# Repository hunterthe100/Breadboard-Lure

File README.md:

# Breadboard-Lure (Not named yet or finished)
A lure for the MinnowBoard Max & MinnowBoard Turbot.  Copyright (C) 2015 Smallworks, LLC

This design is made with [EAGLE CAD](http://www.cadsoftusa.com/eagle-pcb-design-software/about-eagle/) 

This work is licensed under a Creative Commons Attribution-ShareAlike 4.0 International License
[  
*Licensing CC BY-SA 4.0*](http://creativecommons.org/licenses/by-sa/4.0/)

It may be used for Educational, Personal, or Commercial Use, provided you keep these notices,
attribution, and share-alike. When you apply these licenses to material you create, 
it meets the Freedom Defined definition of a "Free Cultural Work". 
Free cultural works are the ones that can be most readily used, shared, 
and remixed by others, and go furthest toward creating a commons of freely reusable materials.

-------------------------------------------------------------------------------------------

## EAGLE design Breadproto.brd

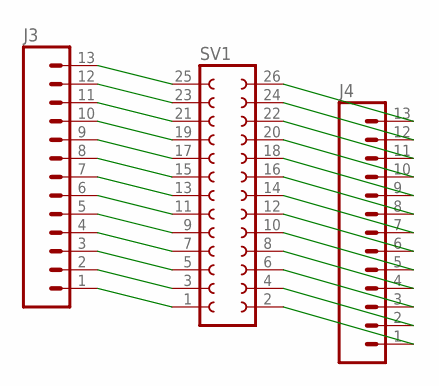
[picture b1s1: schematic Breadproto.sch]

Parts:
J3, J4: M13; 1X13
SV1: FE13-2

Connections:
unnamed: J3.1, SV1.1
unnamed: J3.2, SV1.3
unnamed: J3.3, SV1.5
unnamed: J3.4, SV1.7
unnamed: J3.5, SV1.9
unnamed: J3.6, SV1.11
unnamed: J3.7, SV1.13
unnamed: J3.8, SV1.15
unnamed: J3.9, SV1.17
unnamed: J3.10, SV1.19
unnamed: J3.11, SV1.21
unnamed: J3.12, SV1.23
unnamed: J3.13, SV1.25
unnamed: J4.1, SV1.2
unnamed: J4.2, SV1.4
unnamed: J4.3, SV1.6
unnamed: J4.4, SV1.8
unnamed: J4.5, SV1.10
unnamed: J4.6, SV1.12
unnamed: J4.7, SV1.14
unnamed: J4.8, SV1.16
unnamed: J4.9, SV1.18
unnamed: J4.10, SV1.20
unnamed: J4.11, SV1.22
unnamed: J4.12, SV1.24
unnamed: J4.13, SV1.26

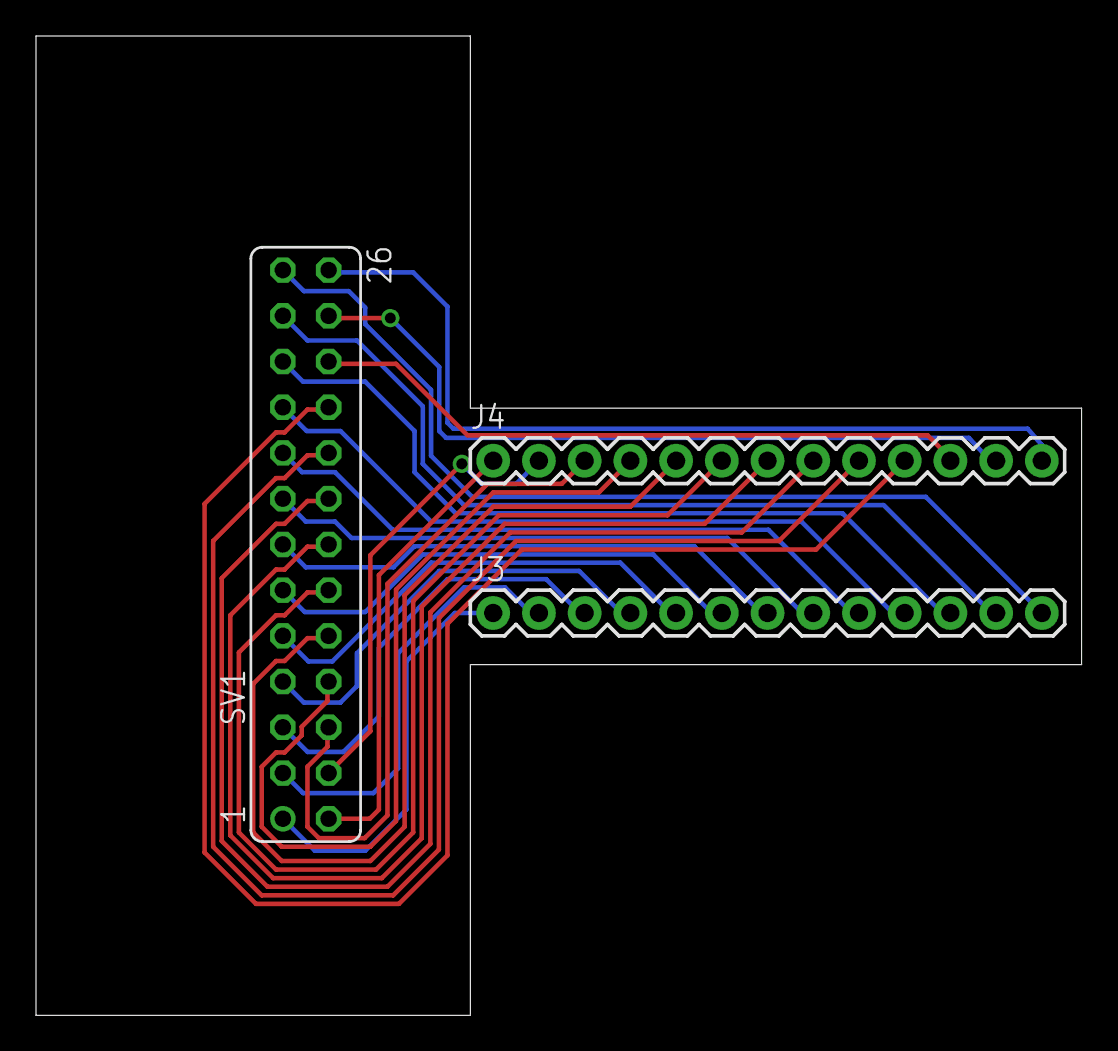
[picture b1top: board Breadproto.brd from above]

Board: 2 copper layers, 58.1 x 54.4 mm, 3 parts (0 on the bottom side), 26 nets.

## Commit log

2016-10-04 Initial Commit
    Breadboard Lure
2016-10-04 added read

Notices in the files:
parts and their libraries:
SparkFun-Connectors: Licensing: Creative Commons ShareAlike 4.0 International - https://creativecommons.org/licenses/by-sa/4.0
